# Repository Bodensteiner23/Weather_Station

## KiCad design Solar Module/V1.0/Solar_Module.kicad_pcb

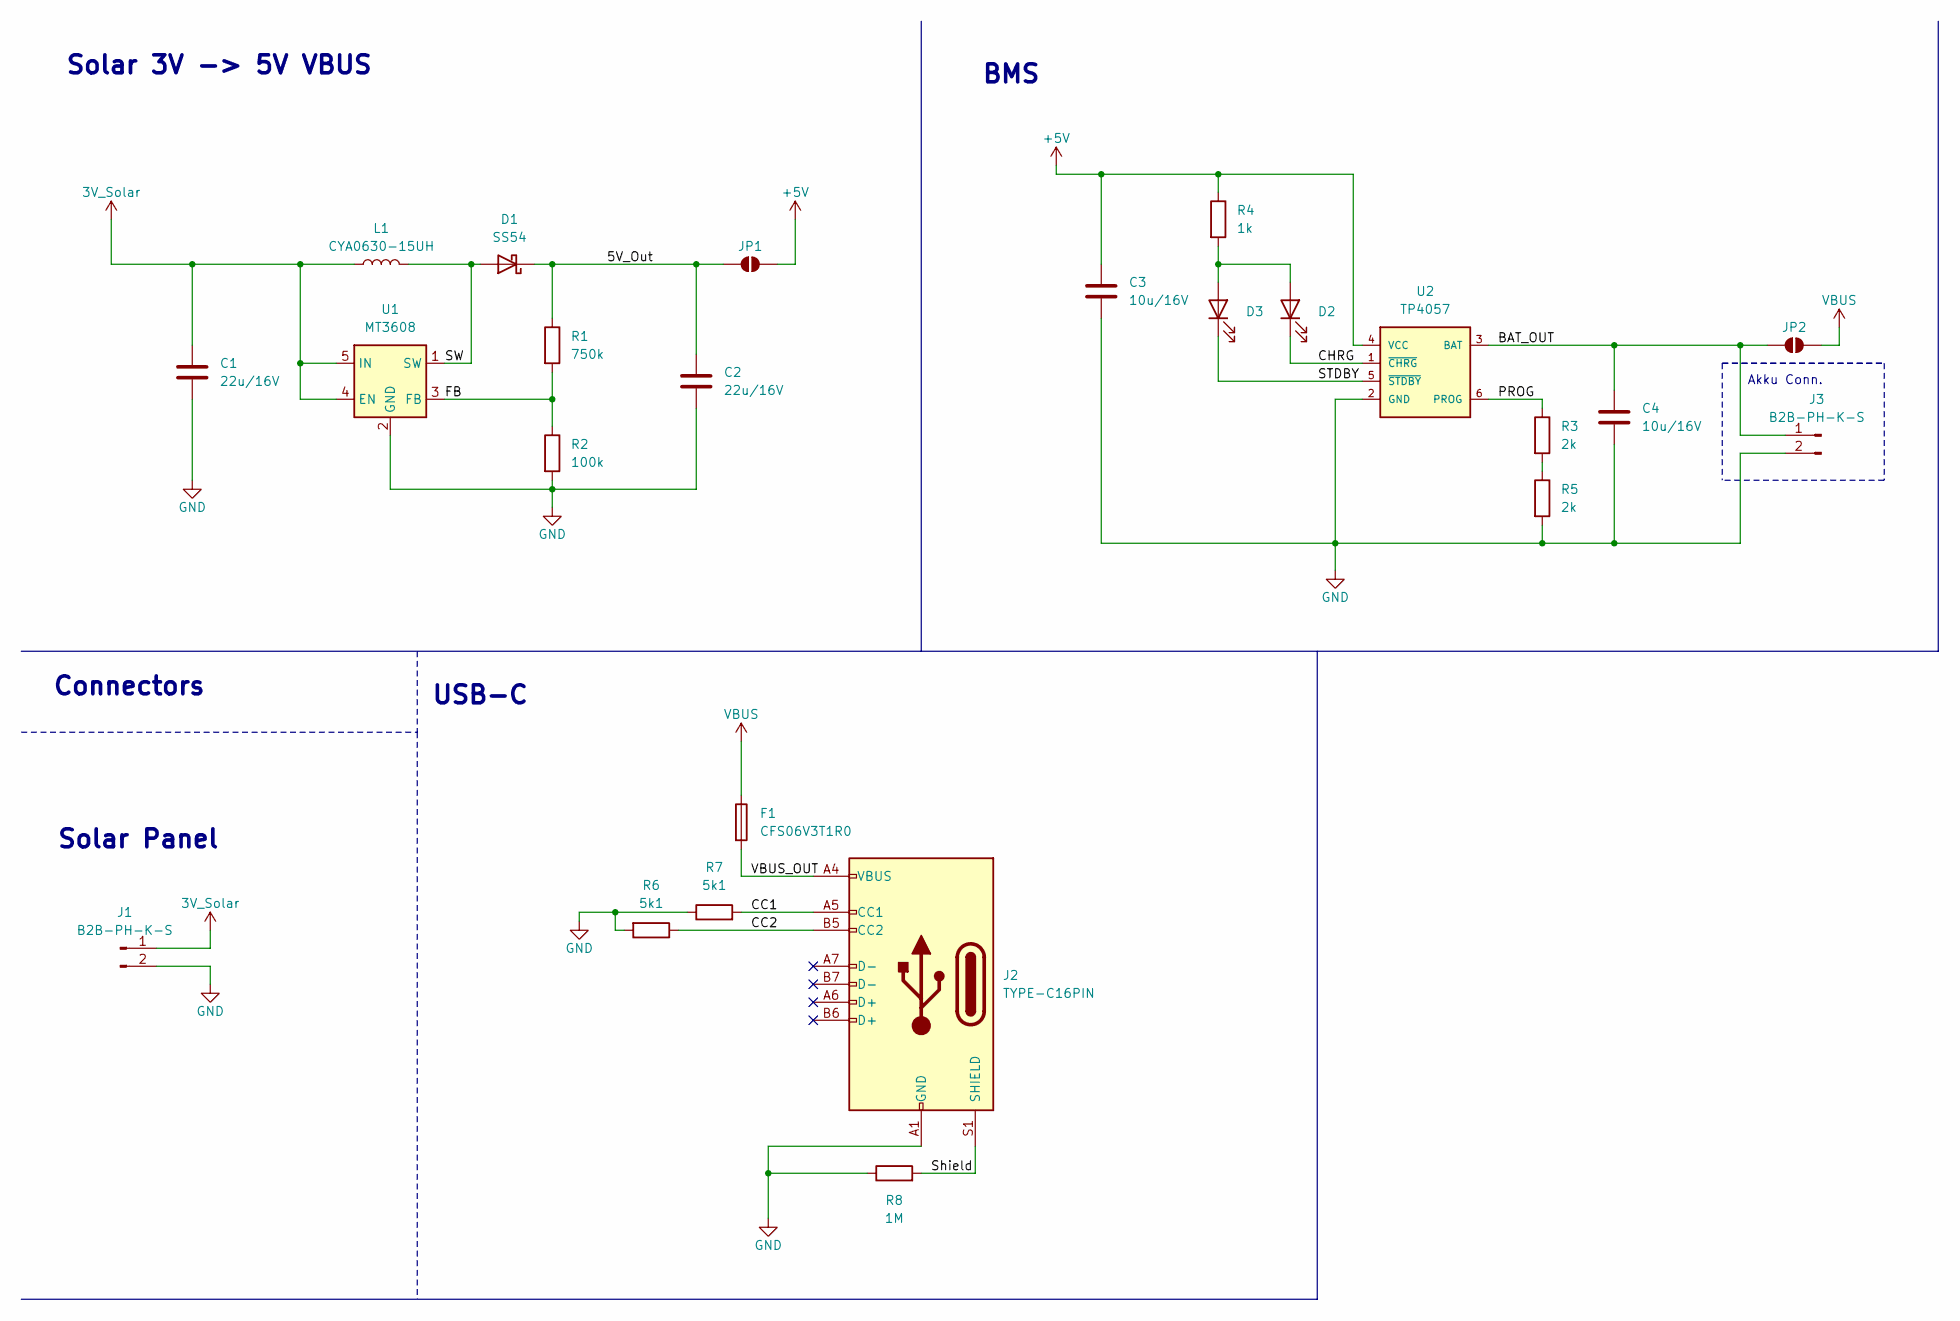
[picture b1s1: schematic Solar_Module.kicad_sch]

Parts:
C1, C2: 22u/16V; C_0805_2012Metric
C3, C4: 10u/16V; C_0805_2012Metric
D1: SS54; D_SMA
D2: KT-0603G; LED_0603_1608Metric
D3: KT-0603R; LED_0603_1608Metric
F1: CFS06V3T1R0; Fuse_0603_1608Metric
J1, J3: B2B-PH-K-S; JST_EH_B2B-EH-A_1x02_P2.50mm_Vertical
J2: TYPE-C16PIN; USB_C_Receptacle_GCT_USB4105-xx-A_16P_TopMnt_Horizontal
JP1, JP2: SolderJumper_2_Open; SolderJumper-2_P1.3mm_Open_TrianglePad1.0x1.5mm
L1: CYA0630-15UH; L_Chilisin_BMRx00060615
R1: 750k; R_0603_1608Metric
R2: 100k; R_0603_1608Metric
R3, R5: 2k; R_0603_1608Metric
R4: 1k; R_0603_1608Metric
R6, R7: 5k1; R_0603_1608Metric
R8: 1M; R_0603_1608Metric
U1: MT3608; SOT-23-6
U2: TP4057; SOT-23-6

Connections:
3V_Solar: C1.1, J1.1, L1.1, U1.4 (EN), U1.5 (IN)
+5V: C3.1, JP1.2 (B), R4.1, U2.4 (VCC)
/5V_Out: C2.1, D1.1 (K), JP1.1 (A), R1.1
/BAT_OUT: C4.1, J3.1, JP2.1 (A), U2.3 (BAT)
/CC1: J2.A5 (CC1), R7.2
/CC2: J2.B5 (CC2), R6.1
/CHRG: D2.1 (K), U2.1 (~CHRG)
/FB: R1.2, R2.1, U1.3 (FB)
/PROG: R3.1, U2.6 (PROG)
/STDBY: D3.1 (K), U2.5 (~STDBY)
/SW: D1.2 (A), L1.2, U1.1 (SW)
/Shield: J2.S1 (SHIELD), R8.2
/VBUS_OUT: F1.2, J2.A4 (VBUS), J2.A9 (VBUS), J2.B4 (VBUS), J2.B9 (VBUS)
GND: C1.2, C2.2, C3.2, C4.2, J1.2, J2.A1 (GND), J2.A12 (GND), J2.B1 (GND), J2.B12 (GND), J3.2, R2.2, R5.2, R6.2, R7.1, R8.1, U1.2 (GND), U2.2 (GND)
unnamed: D2.2 (A), D3.2 (A), R4.2
unnamed: R3.2, R5.1
VBUS: F1.1, JP2.2 (B)

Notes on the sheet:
Solar Panel
Connectors
Akku Conn.
USB-C
BMS
Solar 3V -> 5V VBUS

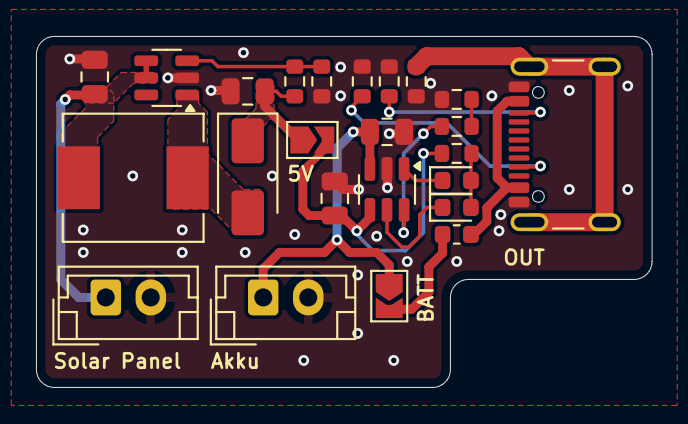
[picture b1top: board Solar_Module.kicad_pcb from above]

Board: 4 copper layers, 34.2 x 19.5 mm, 24 parts (0 on the bottom side), 17 nets.

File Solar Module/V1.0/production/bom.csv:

Designator,Footprint,Quantity,Value,LCSC Part #
"C1, C2",0805,2,22u/16V,
"C3, C4",0805,2,10u/16V,
D1,D_SMA,1,SS54,
"D2, D3",0603,2,LED,
F1,0603,1,CFS06V3T1R0,
"J1, J3",JST_EH_B2B-EH-A_1x02_P2.50mm_Vertical,2,B2B-PH-K-S,
J2,USB_C_Receptacle_GCT_USB4105-xx-A_16P_TopMnt_Horizontal,1,TYPE-C16PIN,
L1,L_Sunlord_MWSA0603S,1,MDA7030-150M,
R1,0603,1,750k,
R2,0603,1,100k,
R3,0603,1,4k,
R4,0603,1,1k,
"R6, R7",0603,2,5k1,
R8,0603,1,1M,
U1,SOT-23-6,1,MT3608,
U2,SOT-23-6,1,TP4057,

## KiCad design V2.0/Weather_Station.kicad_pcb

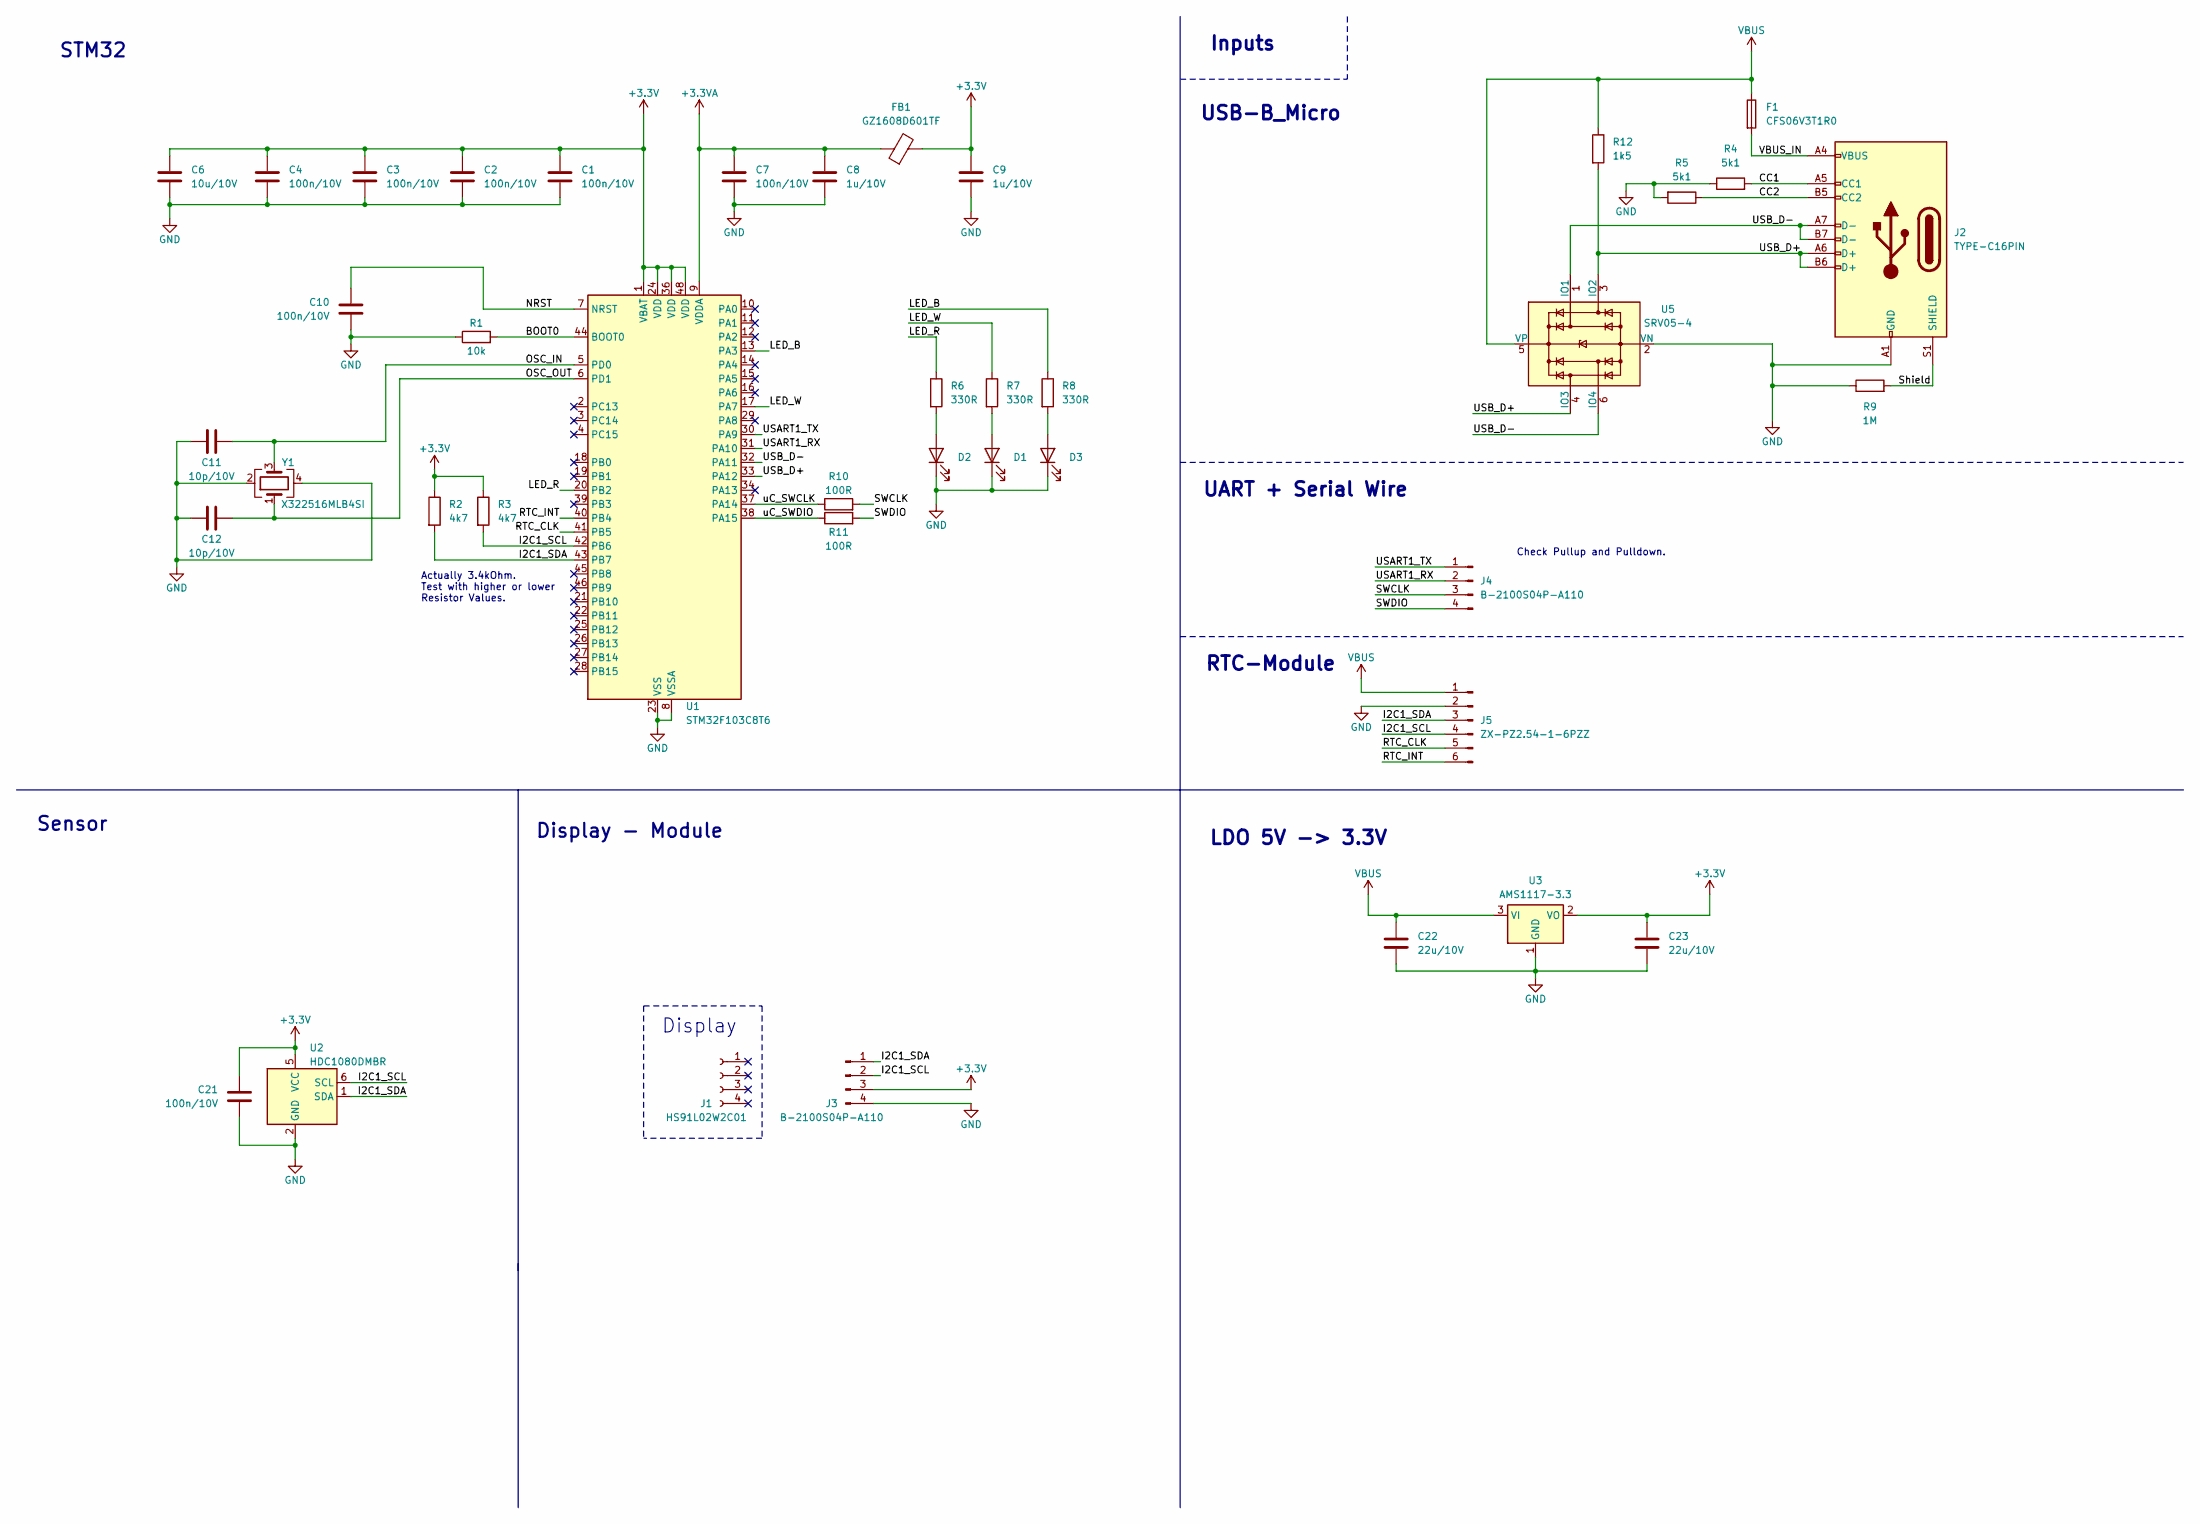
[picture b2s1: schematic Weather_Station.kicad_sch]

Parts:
C1, C2, C3, C4, C7, C10, C21: 100n/10V; C_0603_1608Metric
C6: 10u/10V; C_0805_2012Metric
C8, C9: 1u/10V; C_0603_1608Metric
C11, C12: 10p/10V; C_0603_1608Metric
C22, C23: 22u/10V; C_0805_2012Metric
D1: KT-0603W; LED_0603_1608Metric
D2: KT-0603R; LED_0603_1608Metric
D3: 19-217/BHC-ZL1M2RY/6T; LED_0603_1608Metric
F1: CFS06V3T1R0; Fuse_0603_1608Metric
FB1: GZ1608D601TF; L_0603_1608Metric
J1: HS91L02W2C01; C_0402_1005Metric
J2: TYPE-C16PIN; USB_C_Receptacle_GCT_USB4105-xx-A_16P_TopMnt_Horizontal
J3, J4: B-2100S04P-A110; PinHeader_1x04_P2.54mm_Vertical
J5: ZX-PZ2.54-1-6PZZ; PinHeader_1x06_P2.54mm_Vertical
R1: 10k; R_0603_1608Metric
R2, R3: 4k7; R_0603_1608Metric
R4, R5: 5k1; R_0603_1608Metric
R6, R7, R8: 330R; R_0603_1608Metric
R9: 1M; R_0603_1608Metric
R10, R11: 100R; R_0603_1608Metric
R12: 1k5; R_0603_1608Metric
U1: STM32F103C8T6; LQFP-48_7x7mm_P0.5mm
U2: HDC1080DMBR; Texas_PWSON-N6
U3: AMS1117-3.3; SOT-223-3_TabPin2
U5: SRV05-4; SOT-23-6
Y1: X322516MLB4SI; Crystal_SMD_3225-4Pin_3.2x2.5mm

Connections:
+3.3V: C1.1, C2.1, C3.1, C4.1, C6.1, C9.1, C21.2, C23.1, FB1.2, J3.3, R2.1, R3.1, U1.1 (VBAT), U1.24 (VDD), U1.36 (VDD), U1.48 (VDD), U2.5 (VCC), U3.2 (VO)
+3.3VA: C7.1, C8.1, FB1.1, U1.9 (VDDA)
/BOOT0: R1.2, U1.44 (BOOT0)
/CC1: J2.A5 (CC1), R4.2
/CC2: J2.B5 (CC2), R5.1
/I2C1_SCL: J3.2, J5.4, R3.2, U1.42 (PB6), U2.6 (SCL)
/I2C1_SDA: J3.1, J5.3, R2.2, U1.43 (PB7), U2.1 (SDA)
/LED_B: R8.1, U1.13 (PA3)
/LED_R: R6.1, U1.20 (PB2)
/LED_W: R7.1, U1.17 (PA7)
/NRST: C10.2, U1.7 (NRST)
/OSC_IN: C11.2, U1.5 (PD0), Y1.3
/OSC_OUT: C12.2, U1.6 (PD1), Y1.1
/RTC_CLK: J5.5, U1.41 (PB5)
/RTC_INT: J5.6, U1.40 (PB4)
/SWCLK: J4.3, R10.2
/SWDIO: J4.4, R11.2
/Shield: J2.S1 (SHIELD), R9.2
/USART1_RX: J4.2, U1.31 (PA10)
/USART1_TX: J4.1, U1.30 (PA9)
/USB_D+: J2.A6 (D+), J2.B6 (D+), R12.2, U1.33 (PA12), U5.3 (IO2), U5.4 (IO3)
/USB_D-: J2.A7 (D-), J2.B7 (D-), U1.32 (PA11), U5.1 (IO1), U5.6 (IO4)
/VBUS_IN: F1.2, J2.A4 (VBUS), J2.A9 (VBUS), J2.B4 (VBUS), J2.B9 (VBUS)
/uC_SWCLK: R10.1, U1.37 (PA14)
/uC_SWDIO: R11.1, U1.38 (PA15)
GND: C1.2, C2.2, C3.2, C4.2, C6.2, C7.2, C8.2, C9.2, C10.1, C11.1, C12.1, C21.1, C22.2, C23.2, D1.1 (K), D2.1 (K), D3.1 (K), J2.A1 (GND), J2.A12 (GND), J2.B1 (GND), J2.B12 (GND), J3.4, J5.2, R1.1, R4.1, R5.2, R9.1, U1.8 (VSSA), U1.23 (VSS), U1.35 (VSS), U1.47 (VSS), U2.2 (GND), U3.1 (GND), U5.2 (VN), Y1.2, Y1.4
unnamed: D1.2 (A), R7.2
unnamed: D2.2 (A), R6.2
unnamed: D3.2 (A), R8.2
VBUS: C22.1, F1.1, J5.1, R12.1, U3.3 (VI), U5.5 (VP)

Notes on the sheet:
Inputs
Actually 3.4kOhm. Test with higher or lower Resistor Values.
Display - Module
STM32
Display
Sensor
LDO 5V -> 3.3V
USB-B_Micro
RTC-Module
UART + Serial Wire
Check Pullup and Pulldown.

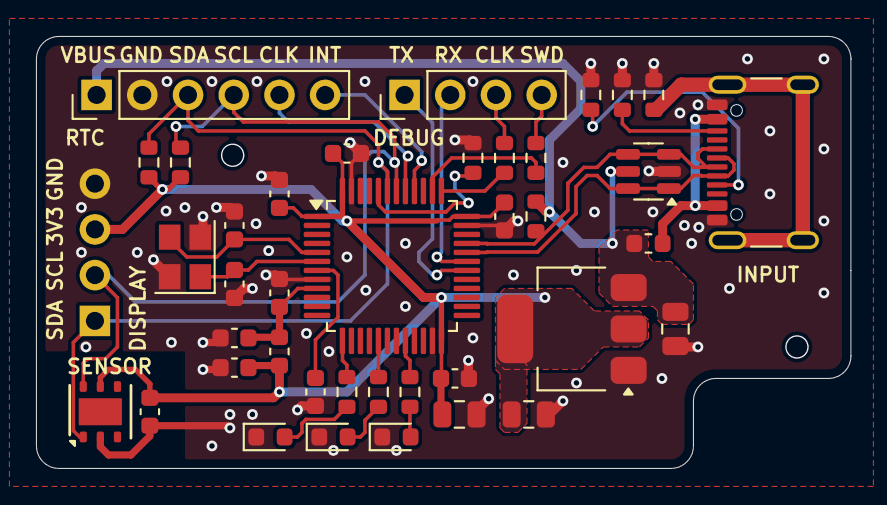
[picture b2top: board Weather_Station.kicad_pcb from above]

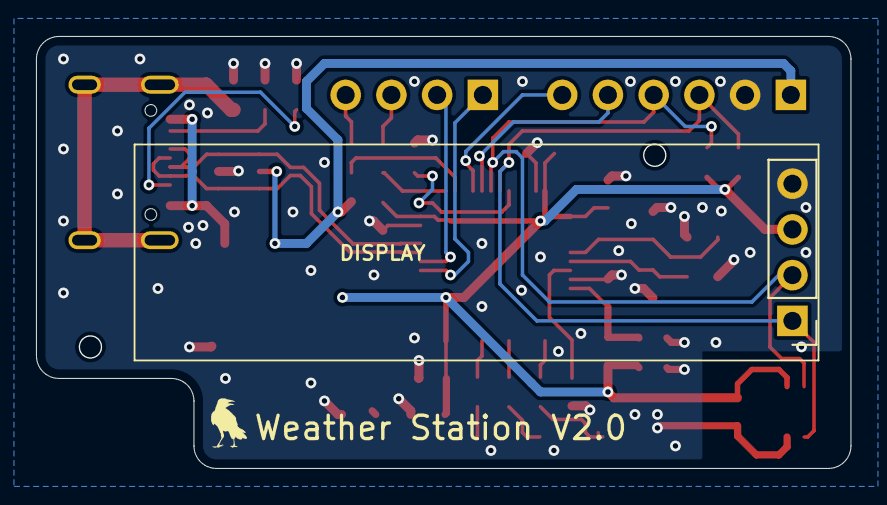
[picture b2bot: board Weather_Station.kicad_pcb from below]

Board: 4 copper layers, 45.2 x 24.0 mm, 41 parts (2 on the bottom side), 30 nets.

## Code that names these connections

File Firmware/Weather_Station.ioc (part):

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Mcu.Name=STM32F103C(8-B)Tx
Mcu.Package=LQFP48
Mcu.UserName=STM32F103C8Tx
PA10.Mode=Asynchronous
PA10.Signal=USART1_RX
PA11.Mode=Device
PA11.Signal=USB_DM
PA12.Mode=Device
PA12.Signal=USB_DP
PA13.GPIOParameters=GPIO_Label
PA13.GPIO_Label=SWDIO
PA13.Mode=Serial_Wire
PA13.Signal=SYS_JTMS-SWDIO
PA14.GPIOParameters=GPIO_Label
PA14.GPIO_Label=SWCLK
PA14.Mode=Serial_Wire
PA14.Signal=SYS_JTCK-SWCLK
PA3.GPIOParameters=GPIO_Label
PA3.GPIO_Label=LED_RED
PA3.Signal=GPIO_Output
PA9.Mode=Asynchronous
PA9.Signal=USART1_TX
PB6.Mode=I2C
PB6.Signal=I2C1_SCL
PB7.Mode=I2C
PB7.Signal=I2C1_SDA
PD0-OSC_IN.Mode=HSE-External-Oscillator
PD0-OSC_IN.Signal=RCC_OSC_IN
PD1-OSC_OUT.Mode=HSE-External-Oscillator
PD1-OSC_OUT.Signal=RCC_OSC_OUT
RCC.HSE_VALUE=16000000
RCC.SYSCLKFreq_VALUE=16000000
RCC.SYSCLKSource=RCC_SYSCLKSOURCE_HSE
board=custom

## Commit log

2024-07-30 Initall commit of project.
2024-07-30 Finished pricipal routing of STM32F103.
2024-07-30 Added STM32 Fiormware Directory + Prj. . Added OSC.
2024-07-31 Some changes in the IOC and continues Schematic.
2024-07-31 Display Wiring should be finsihed.
2024-07-31 Now Display should be finished.
2024-07-31 Just added input capacitor to sensor.
2024-08-01 Added Step File of Sensor. USB Section should be finished and be ready for design.
2024-08-01 Updated Schematic with corrected TVS section.
2024-08-01 Now wiring of USB should be correct.
2024-08-01 Schematic should be 90% finished. Finishing touches and then design review.
2024-08-01 Weird schematic error fixed.
2024-08-01 Added Debug Leds.
2024-08-01 Started Layout of PCB.
2024-08-01 Made Progress with STM32 Layout.
2024-08-02 Changed USART1 to USART3. Finished LDO Layout. Finished ESD protection of micro USB.
2024-08-02 Changed back to USART_1.
2024-08-02 Questions for Schwering now.
2024-08-04 Decided to not go with the display. Added Step file for display.
2024-08-04 Should be final component placement.
2024-08-04 Finished first version of routing.
2024-08-04 Changed Micro USB to USB.
2024-08-04 Routing of V1 should be finsihed.
2024-08-04 V1.0 should be finished.
2024-08-04 DRC is to do but otherwise should be V1.
2024-08-05 Changed Fuse and added SWD Restistor.
2024-08-06 Added v2 of project.
2024-08-06 Progressed with much more cleaner design.
2024-08-06 Made Progress with Design of V2.
2024-08-06 Nearly finished V2.
2024-08-06 V2 nerly finished. Round corners / DRC need to be done.
2024-08-06 V2 should be finished!!
2024-08-06 This is ordered Version of Weather Station V2!!!
2024-08-07 Added ToDo for next Version.
2024-08-07 Changed Directory and added sub directories for different pcbs.
2024-08-07 Design of MT3608 Boost converter should be finished.
2024-08-07 Added TP4057 to Schematic.
2024-08-08 Updated Buck Converter Passives.
2024-08-08 Schematic of TP4057 should be finished.
2024-08-08 Added Connector for Akku.
2024-08-10 Added USB-C connector to schematic.
2024-08-10 Updated Schematics and nearly finished schematic.
2024-08-10 Rough design of DCDC.
2024-08-10 Continued with layout of BMS IC.
2024-08-11 Progressed with Design. Now in a solid state.
2024-08-11 Design roughly finished. Now Routing.
2024-08-11 V1 Design nearly finished. Only Edges needed to be round.
2024-08-11 Design should be finished.
2024-08-12 Added BOM_Tool.
2024-08-12 Added Production files.
2024-08-12 Updated Script.
2024-08-14 Added BOMS and added notes in schematic.
2024-08-16 Nothing really changed.
2024-08-16 Changed Script
2024-08-16 Final Script
2024-08-16 Final BOM.
2024-08-16 This is ordered Version!!!
2024-08-17 Started with readout function.
2024-08-17 Should be IOC.
2024-08-19 HDC1080 Prototype should be finished.
2024-08-19 Updated GitIgnore.
2024-08-19 And added Debug.
2024-08-19 Deleted Debug Folder.
2024-08-19 Now HDC1080 Prototype should be finsihed.
2024-08-20 Added Display Driver to project.
2024-08-22 Started to work on RTC_
2024-08-22 Added .vscode for editing.
2024-08-23 RTC code should be finished.
2024-08-23 Added some code for weather station.
2024-08-23 Fixed Include Problems.
2024-08-24 Changed Clock.
2024-09-04 Added debug LED.
2024-09-05 Working Version of reading out Sensor Data!
2024-09-05 Working Version of Plotting Sensor Data with UART.
2024-09-06 Working Version of plotting data via display.
